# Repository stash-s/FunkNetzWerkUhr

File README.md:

# FunkNetzWerkUhr
ESP8266 IN-12 Nixie lamp netwok clock

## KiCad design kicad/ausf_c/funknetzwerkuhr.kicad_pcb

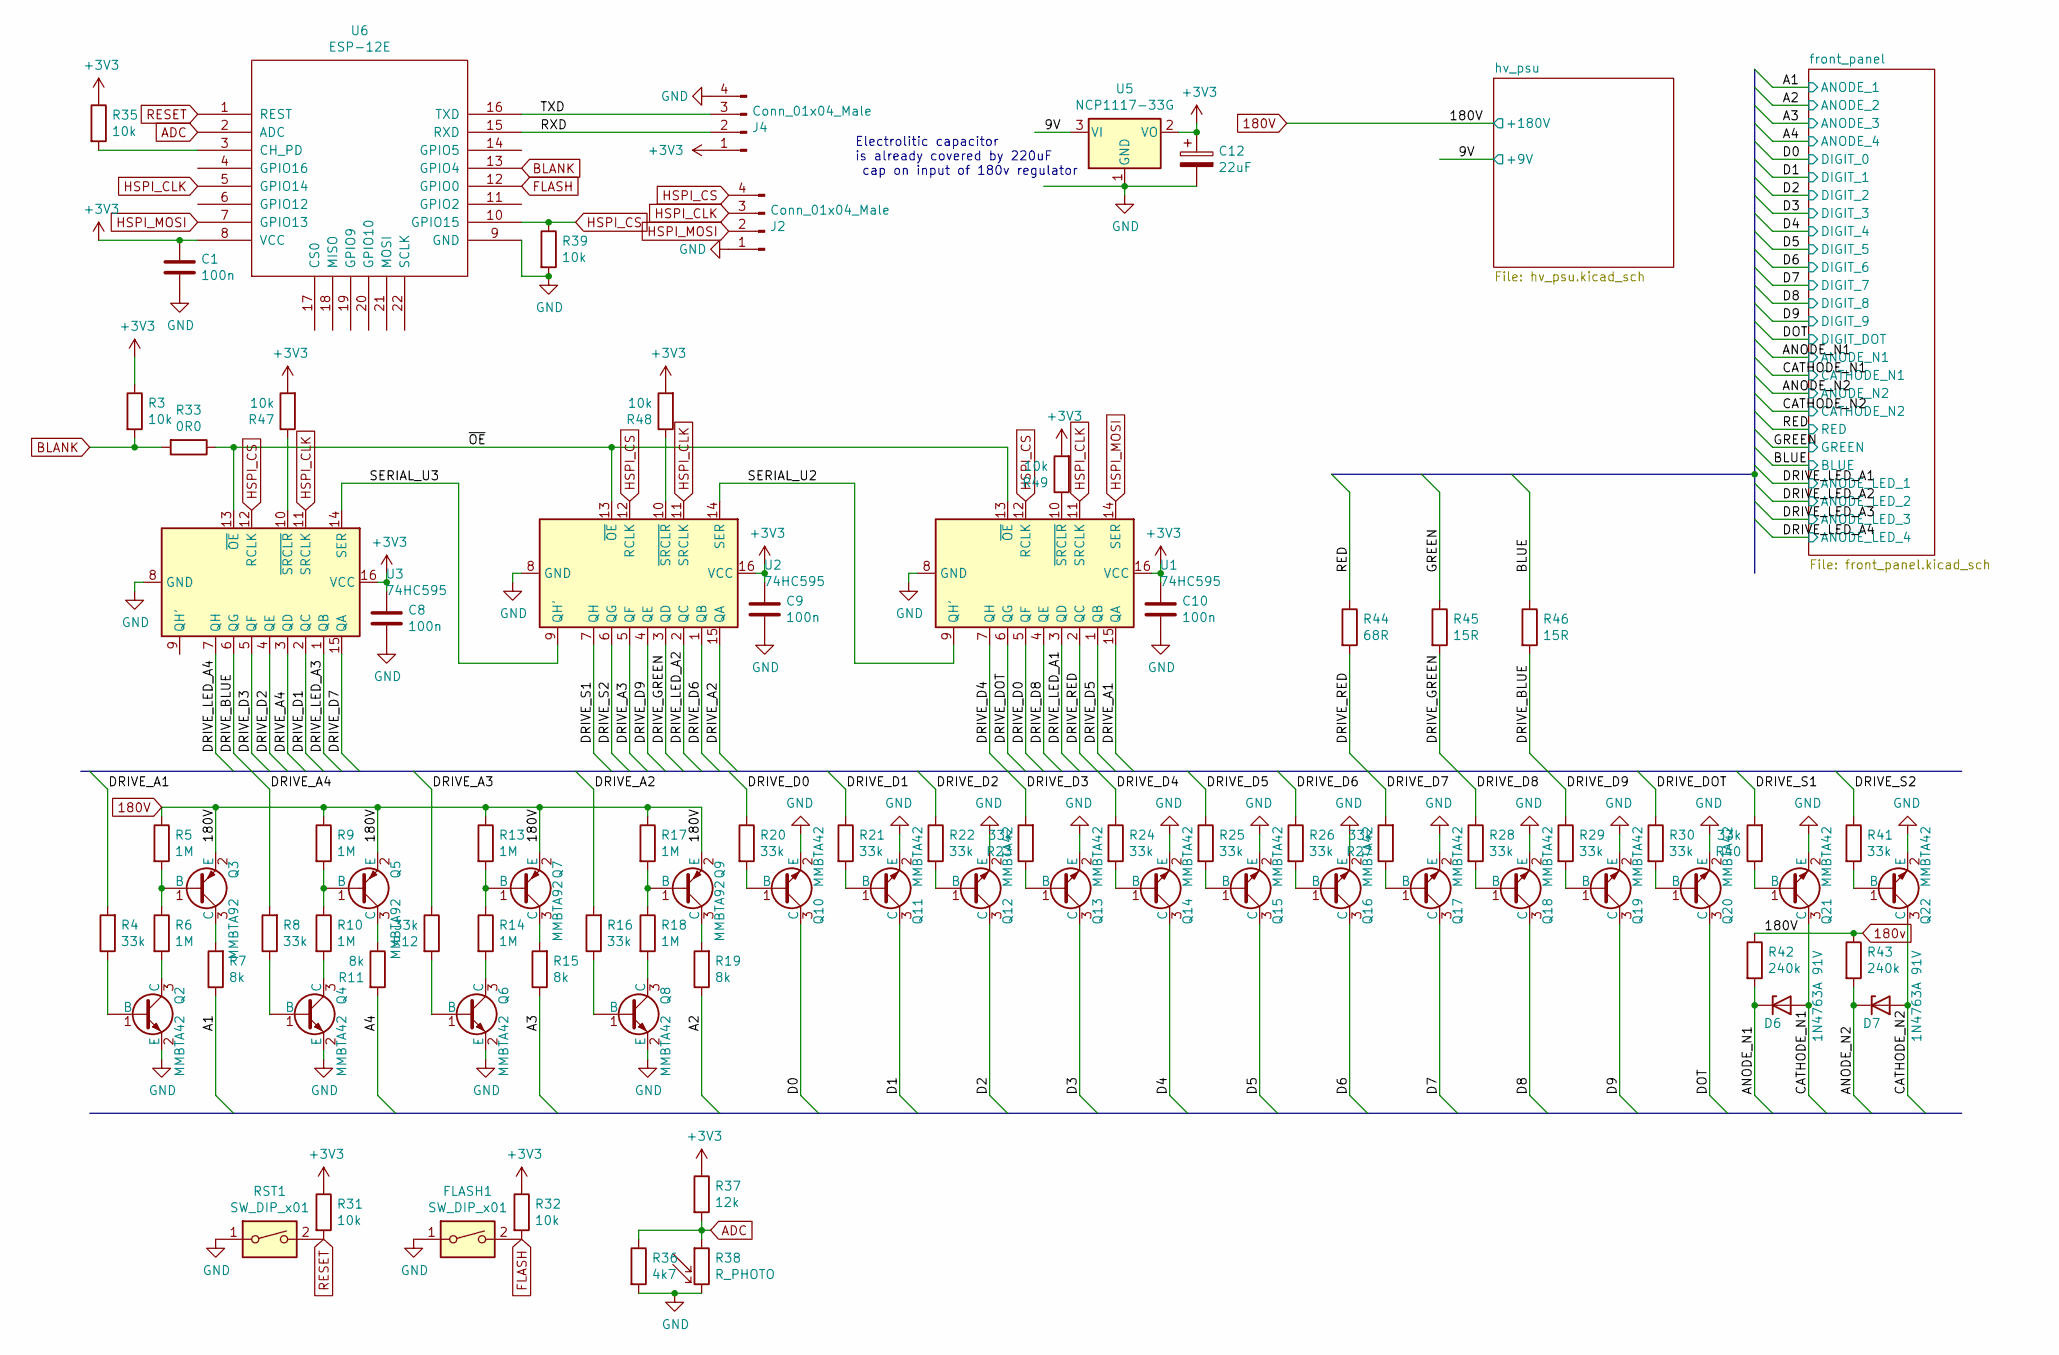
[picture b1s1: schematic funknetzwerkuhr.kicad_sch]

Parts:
C1, C8, C9, C10: 100n; C_1206_3216Metric_Pad1.42x1.75mm_HandSolder
C12: 22uF; CP_Radial_D6.3mm_P2.50mm
D6, D7: 1N4763A 91V; D_MiniMELF_Handsoldering
FLASH1: SW_DIP_x01; SW_PUSH-12mm
J2: Conn_01x04_Male; PinHeader_1x04_P2.54mm_Vertical
J4: Conn_01x04_Male; PinHeader_1x04_P2.54mm_Horizontal
Q2, Q4, Q6, Q8, Q10, Q11, Q12, Q13, Q14, Q15, Q16, Q17, Q18, Q19, Q20, Q21, Q22: MMBTA42; MPSA42-TSOT-23_HandSoldering
Q3, Q5, Q7, Q9: MMBTA92; MPSA92-TSOT-23_HandSoldering
R3, R31, R32, R35, R39, R47, R48, R49: 10k; R_0805_2012Metric_Pad1.15x1.40mm_HandSolder_Value
R4, R8, R12, R16, R20, R21, R22, R23, R24, R25, R26, R27, R28, R29, R30, R40, R41: 33k; R_0805_2012Metric_Pad1.15x1.40mm_HandSolder_Value
R5, R6, R9, R10, R13, R14, R17, R18: 1M; R_0805_2012Metric_Pad1.15x1.40mm_HandSolder_Value
R7, R11, R15, R19: 8k; R_0805_2012Metric_Pad1.15x1.40mm_HandSolder_Value
R33: 0R0; R_0805_2012Metric_Pad1.15x1.40mm_HandSolder_Value
R36: 4k7; R_0805_2012Metric_Pad1.15x1.40mm_HandSolder_Value
R37: 12k; R_0805_2012Metric_Pad1.15x1.40mm_HandSolder_Value
R38: R_PHOTO; R_LDR_4.9x4.2mm_P2.54mm_Vertical
R42, R43: 240k; R_0805_2012Metric_Pad1.15x1.40mm_HandSolder_Value
R44: 68R; R_0805_2012Metric_Pad1.15x1.40mm_HandSolder_Value
R45, R46: 15R; R_0805_2012Metric_Pad1.15x1.40mm_HandSolder_Value
RST1: SW_DIP_x01; SW_PUSH-12mm
U1, U2, U3: 74HC595; SOIC-16_3.9x9.9mm_P1.27mm
U5: NCP1117-33G; DPACK2
U6: ESP-12E; ESP-12E_SMD

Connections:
180V: Q3.2 (E), Q5.2 (E), Q7.2 (E), Q9.2 (E), R5.1, R9.1, R13.1, R17.1, R42.1, R43.1; also elsewhere on the board
+3V3: C1.1, C8.1, C9.1, C10.1, C12.1, J4.1, R3.1, R31.1, R32.1, R35.1, R37.1, R47.2, R48.2, R49.2, U1.16 (VCC), U2.16 (VCC), U3.16 (VCC), U5.2 (VO), U6.8 (VCC)
+9V: U5.3 (VI); also elsewhere on the board
/A1: R7.1; also elsewhere on the board
/A2: R19.1; also elsewhere on the board
/A3: R15.1; also elsewhere on the board
/A4: R11.2; also elsewhere on the board
/ANODE_N1: D6.1 (K), R42.2; also elsewhere on the board
/ANODE_N2: D7.1 (K), R43.2; also elsewhere on the board
/BLUE: R46.1; also elsewhere on the board
/CATHODE_N1: D6.2 (A), Q21.3 (C); also elsewhere on the board
/CATHODE_N2: D7.2 (A), Q22.3 (C); also elsewhere on the board
/D0: Q10.3 (C); also elsewhere on the board
/D1: Q11.3 (C); also elsewhere on the board
/D2: Q12.3 (C); also elsewhere on the board
/D3: Q13.3 (C); also elsewhere on the board
/D4: Q14.3 (C); also elsewhere on the board
/D5: Q15.3 (C); also elsewhere on the board
/D6: Q16.3 (C); also elsewhere on the board
/D7: Q17.3 (C); also elsewhere on the board
/D8: Q18.3 (C); also elsewhere on the board
/D9: Q19.3 (C); also elsewhere on the board
/DOT: Q20.3 (C); also elsewhere on the board
/DRIVE_A1: R4.2, U1.15 (QA)
/DRIVE_A2: R16.2, U2.15 (QA)
/DRIVE_A3: R12.1, U2.5 (QF)
/DRIVE_A4: R8.2, U3.3 (QD)
/DRIVE_BLUE: R46.2, U3.6 (QG)
/DRIVE_D0: R20.1, U1.5 (QF)
/DRIVE_D1: R21.1, U3.2 (QC)
/DRIVE_D2: R22.1, U3.4 (QE)
/DRIVE_D3: R23.2, U3.5 (QF)
/DRIVE_D4: R24.1, U1.7 (QH)
/DRIVE_D5: R25.1, U1.1 (QB)
/DRIVE_D6: R26.1, U2.1 (QB)
/DRIVE_D7: R27.2, U3.15 (QA)
/DRIVE_D8: R28.1, U1.4 (QE)
/DRIVE_D9: R29.1, U2.4 (QE)
/DRIVE_DOT: R30.1, U1.6 (QG)
/DRIVE_GREEN: R45.2, U2.3 (QD)
/DRIVE_LED_A1: U1.3 (QD); also elsewhere on the board
/DRIVE_LED_A2: U2.2 (QC); also elsewhere on the board
/DRIVE_LED_A3: U3.1 (QB); also elsewhere on the board
/DRIVE_LED_A4: U3.7 (QH); also elsewhere on the board
/DRIVE_RED: R44.2, U1.2 (QC)
/DRIVE_S1: R40.2, U2.7 (QH)
/DRIVE_S2: R41.1, U2.6 (QG)
/GREEN: R45.1; also elsewhere on the board
/RED: R44.1; also elsewhere on the board
/RXD: J4.2, U6.15 (RXD)
/SERIAL_U2: U1.9 (QH'), U2.14 (SER)
/SERIAL_U3: U2.9 (QH'), U3.14 (SER)
/TXD: J4.3, U6.16 (TXD)
/~OE: R33.1, U1.13 (~OE), U2.13 (~OE), U3.13 (~OE)
ADC: R36.1, R37.2, R38.1, U6.2 (ADC)
BLANK: R3.2, R33.2, U6.13 (GPIO4); also elsewhere on the board
FLASH: FLASH1.2, R32.2, U6.12 (GPIO0)
GND: C1.2, C8.2, C9.2, C10.2, C12.2, FLASH1.1, J2.1, J4.4, Q2.2 (E), Q4.2 (E), Q6.2 (E), Q8.2 (E), Q10.2 (E), Q11.2 (E), Q12.2 (E), Q13.2 (E), Q14.2 (E), Q15.2 (E), Q16.2 (E), Q17.2 (E), Q18.2 (E), Q19.2 (E), Q20.2 (E), Q21.2 (E), Q22.2 (E), R36.2, R38.2, R39.2, RST1.1, U1.8 (GND), U2.8 (GND), U3.8 (GND), U5.1 (GND), U6.9 (GND); also elsewhere on the board
HSPI_CLK: J2.3, U1.11 (SRCLK), U2.11 (SRCLK), U3.11 (SRCLK), U6.5 (GPIO14)
HSPI_CS: J2.4, R39.1, U1.12 (RCLK), U2.12 (RCLK), U3.12 (RCLK), U6.10 (GPIO15)
HSPI_MOSI: J2.2, U1.14 (SER), U6.7 (GPIO13)
unnamed: Q2.1 (B), R4.1
unnamed: Q2.3 (C), R6.2
unnamed: Q3.1 (B), R5.2, R6.1
unnamed: Q3.3 (C), R7.2
unnamed: Q4.1 (B), R8.1
unnamed: Q4.3 (C), R10.2
unnamed: Q5.1 (B), R9.2, R10.1
unnamed: Q5.3 (C), R11.1
unnamed: Q6.1 (B), R12.2
unnamed: Q6.3 (C), R14.2
unnamed: Q7.1 (B), R13.2, R14.1
unnamed: Q7.3 (C), R15.2
unnamed: Q8.1 (B), R16.1
unnamed: Q8.3 (C), R18.2
unnamed: Q9.1 (B), R17.2, R18.1
unnamed: Q9.3 (C), R19.2
unnamed: Q10.1 (B), R20.2
unnamed: Q11.1 (B), R21.2
unnamed: Q12.1 (B), R22.2
unnamed: Q13.1 (B), R23.1
unnamed: Q14.1 (B), R24.2
unnamed: Q15.1 (B), R25.2
unnamed: Q16.1 (B), R26.2
unnamed: Q17.1 (B), R27.1
unnamed: Q18.1 (B), R28.2
unnamed: Q19.1 (B), R29.2
unnamed: Q20.1 (B), R30.2
unnamed: Q21.1 (B), R40.1
unnamed: Q22.1 (B), R41.2
unnamed: R35.2, U6.3 (CH_PD)
unnamed: R47.1, U3.10 (~SRCLR)
unnamed: R48.1, U2.10 (~SRCLR)
unnamed: R49.1, U1.10 (~SRCLR)
RESET: R31.2, RST1.2, U6.1 (REST)

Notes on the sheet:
Electrolitic capacitor is already covered by 220uF cap on input of 180v regulator

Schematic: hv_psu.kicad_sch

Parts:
C2, C3: 100n; C_1206_3216Metric_Pad1.42x1.75mm_HandSolder
C4: 220uF,25V; CP_Radial_D10.0mm_P2.50mm_P5.00mm
C5: 4.7uF,250V; CP_Radial_D8.0mm_P3.50mm
C7: 100n,250V; C_Rect_L16.5mm_W4.7mm_P15.00mm_MKT
D1: ES2J; D_SMB_Handsoldering
J1: Jack-DC; AliExpress55mmBarelJack
J3: Conn_01x02_Male; PinHeader_1x02_P2.54mm_Vertical
L1: L; L_Toroid_Vertical_L14.0mm_W6.3mm_P4.57mm_Pulse_A
Q1: IRF640; TO-263-2
R1: 1.5M; R_1206_3216Metric_Pad1.42x1.75mm_HandSolder
R1a1: 2.7k; R_0805_2012Metric_Pad1.15x1.40mm_HandSolder_Value
R2: 10k; R_0805_2012Metric_Pad1.15x1.40mm_HandSolder_Value
R34: 0R0; R_0805_2012Metric_Pad1.15x1.40mm_HandSolder_Value
RSENSE1: 0R1; R_2512_6332Metric_Pad1.52x3.35mm_HandSolder
U4: max1771; PowerIntegrations_SO-8

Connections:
180V: C5.1, C7.1, D1.1 (K), J3.2, R1.1; also elsewhere on the board
+9V: C2.1, C4.1, J1.1, L1.1, U4.2 (VCC); also elsewhere on the board
/hv_psu/SENSE: Q1.3 (S), RSENSE1.1, U4.8 (CS)
BLANK: R34.2; also elsewhere on the board
GND: C2.2, C3.2, C4.2, C5.2, C7.2, J1.2, J1.3, J3.1, R2.2, RSENSE1.2, U4.6 (AGND), U4.7 (GND); also elsewhere on the board
unnamed: C3.1, U4.5 (REF)
unnamed: D1.2 (A), L1.2, Q1.2 (D)
unnamed: Q1.1 (G), U4.1 (EXT)
unnamed: R1.2, R1a1.1, U4.3 (FB)
unnamed: R1a1.2, R2.1
unnamed: R34.1, U4.4 (SHDN)

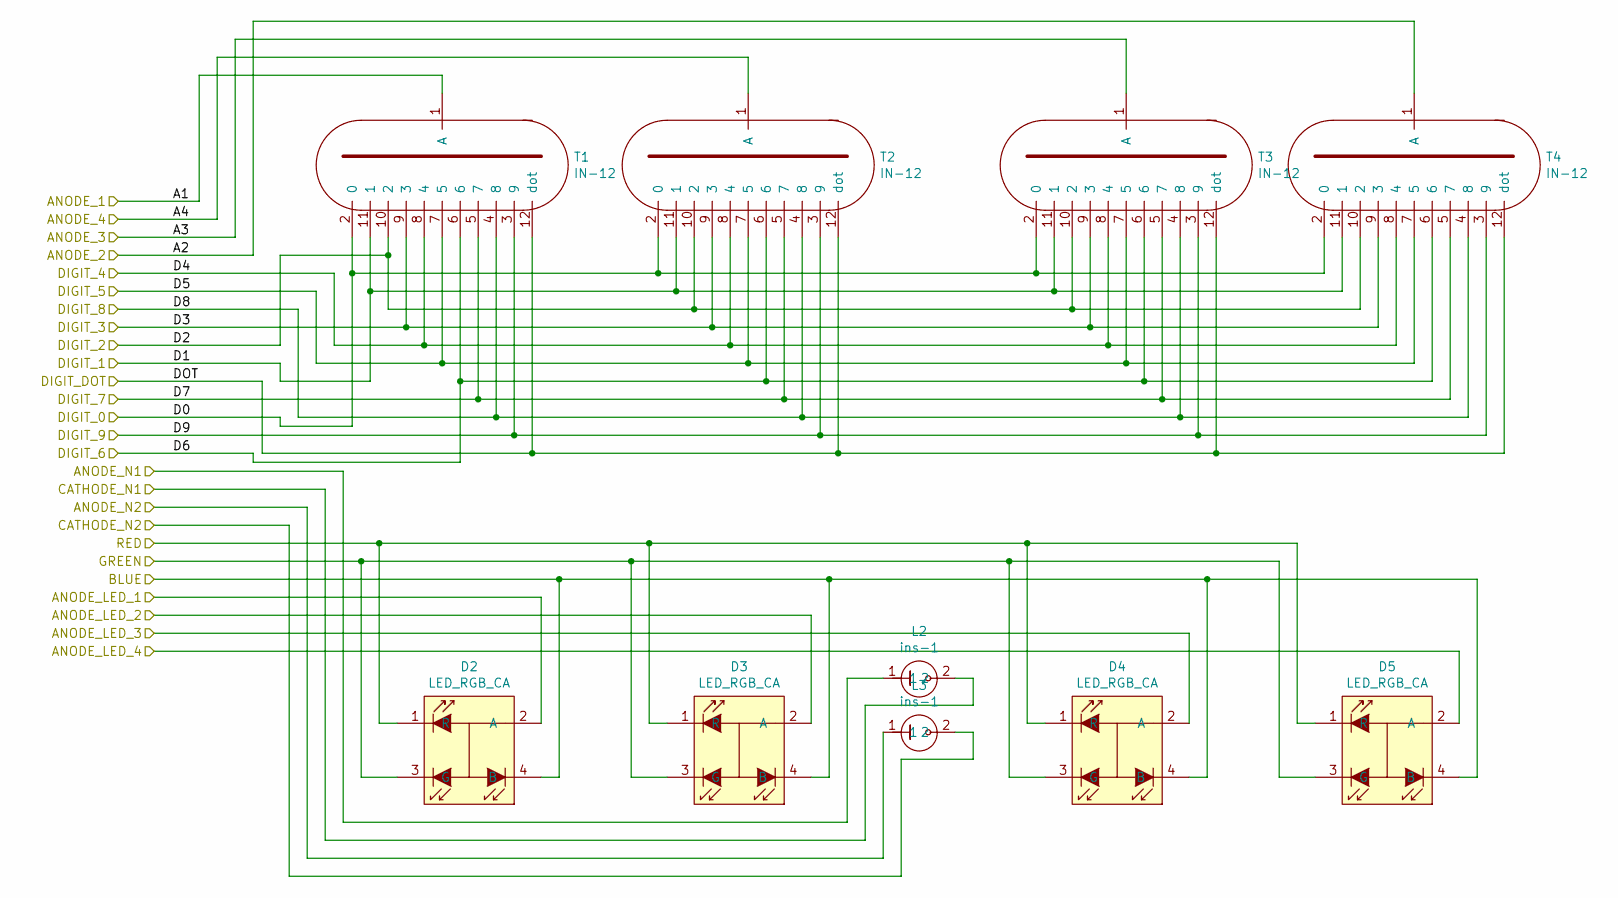
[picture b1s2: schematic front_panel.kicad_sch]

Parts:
D2, D3, D4, D5: LED_RGB_CA; LED_3528_3.5x2.8mm
L2, L3: ins-1
T1, T2, T3, T4: IN-12; IN-12_0.8mm_simple

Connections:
/A1: T1.1 (A); also elsewhere on the board
/A2: T4.1 (A); also elsewhere on the board
/A3: T3.1 (A); also elsewhere on the board
/A4: T2.1 (A); also elsewhere on the board
/ANODE_N1: L2.1; also elsewhere on the board
/ANODE_N2: L3.1; also elsewhere on the board
/BLUE: D2.4 (B), D3.4 (B), D4.4 (B), D5.4 (B); also elsewhere on the board
/CATHODE_N1: L2.2; also elsewhere on the board
/CATHODE_N2: L3.2; also elsewhere on the board
/D0: T1.2 (0), T2.2 (0), T3.2 (0), T4.2 (0); also elsewhere on the board
/D1: T1.11 (1), T2.11 (1), T3.11 (1), T4.11 (1); also elsewhere on the board
/D2: T1.10 (2), T2.10 (2), T3.10 (2), T4.10 (2); also elsewhere on the board
/D3: T1.9 (3), T2.9 (3), T3.9 (3), T4.9 (3); also elsewhere on the board
/D4: T1.8 (4), T2.8 (4), T3.8 (4), T4.8 (4); also elsewhere on the board
/D5: T1.7 (5), T2.7 (5), T3.7 (5), T4.7 (5); also elsewhere on the board
/D6: T1.6, T2.6, T3.6, T4.6; also elsewhere on the board
/D7: T1.5 (7), T2.5 (7), T3.5 (7), T4.5 (7); also elsewhere on the board
/D8: T1.4 (8), T2.4 (8), T3.4 (8), T4.4 (8); also elsewhere on the board
/D9: T1.3 (9), T2.3 (9), T3.3 (9), T4.3 (9); also elsewhere on the board
/DOT: T1.12 (dot), T2.12 (dot), T3.12 (dot), T4.12 (dot); also elsewhere on the board
/DRIVE_LED_A1: D2.2 (A); also elsewhere on the board
/DRIVE_LED_A2: D3.2 (A); also elsewhere on the board
/DRIVE_LED_A3: D4.2 (A); also elsewhere on the board
/DRIVE_LED_A4: D5.2 (A); also elsewhere on the board
/GREEN: D2.3 (G), D3.3 (G), D4.3 (G), D5.3 (G); also elsewhere on the board
/RED: D2.1 (R), D3.1 (R), D4.1 (R), D5.1 (R); also elsewhere on the board

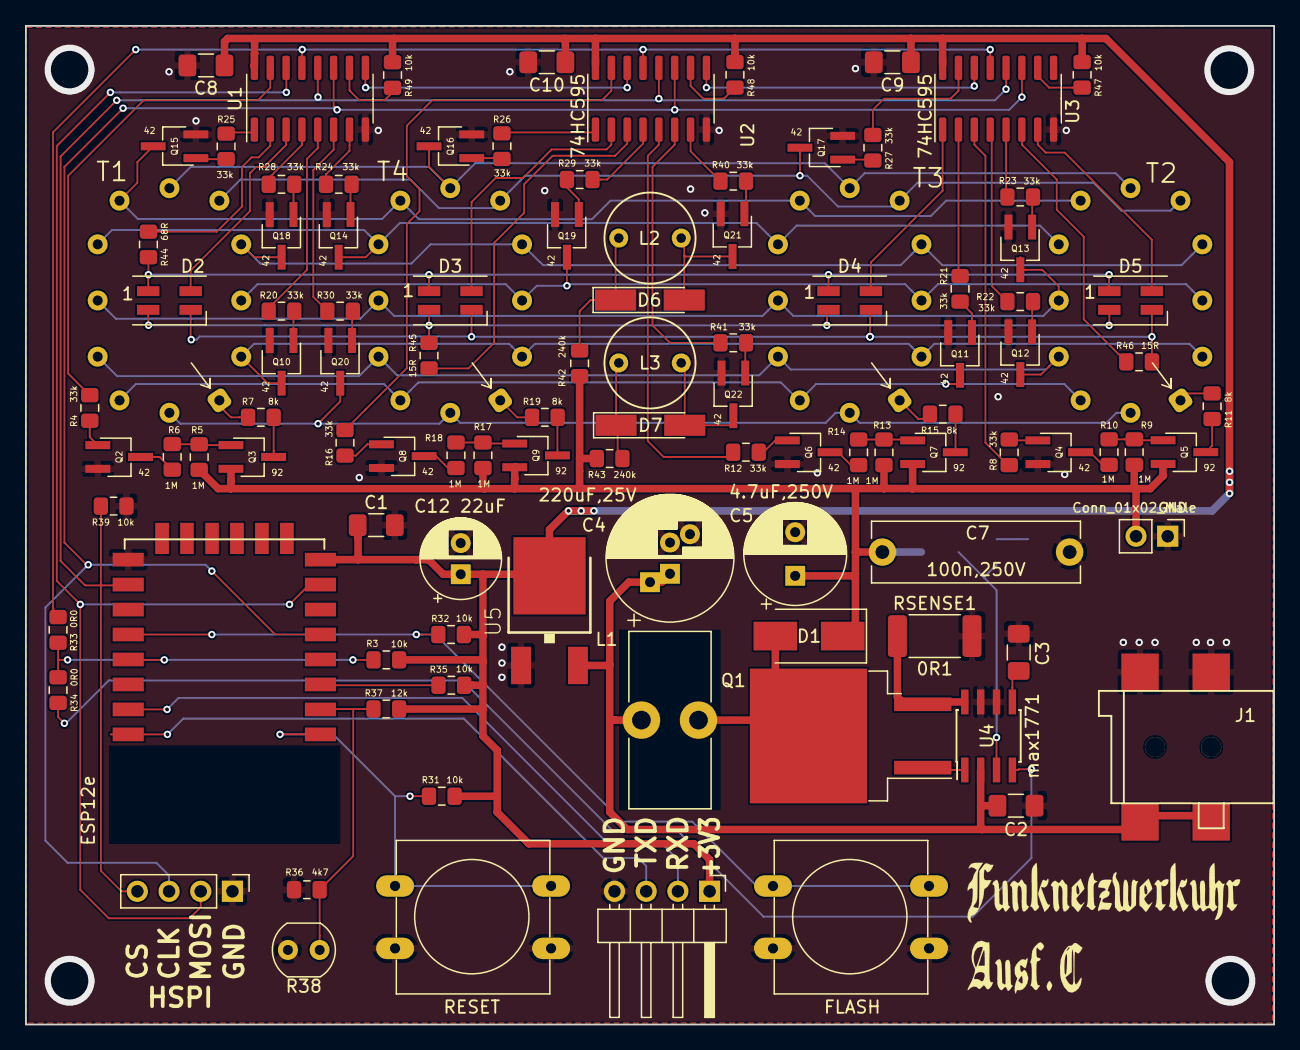
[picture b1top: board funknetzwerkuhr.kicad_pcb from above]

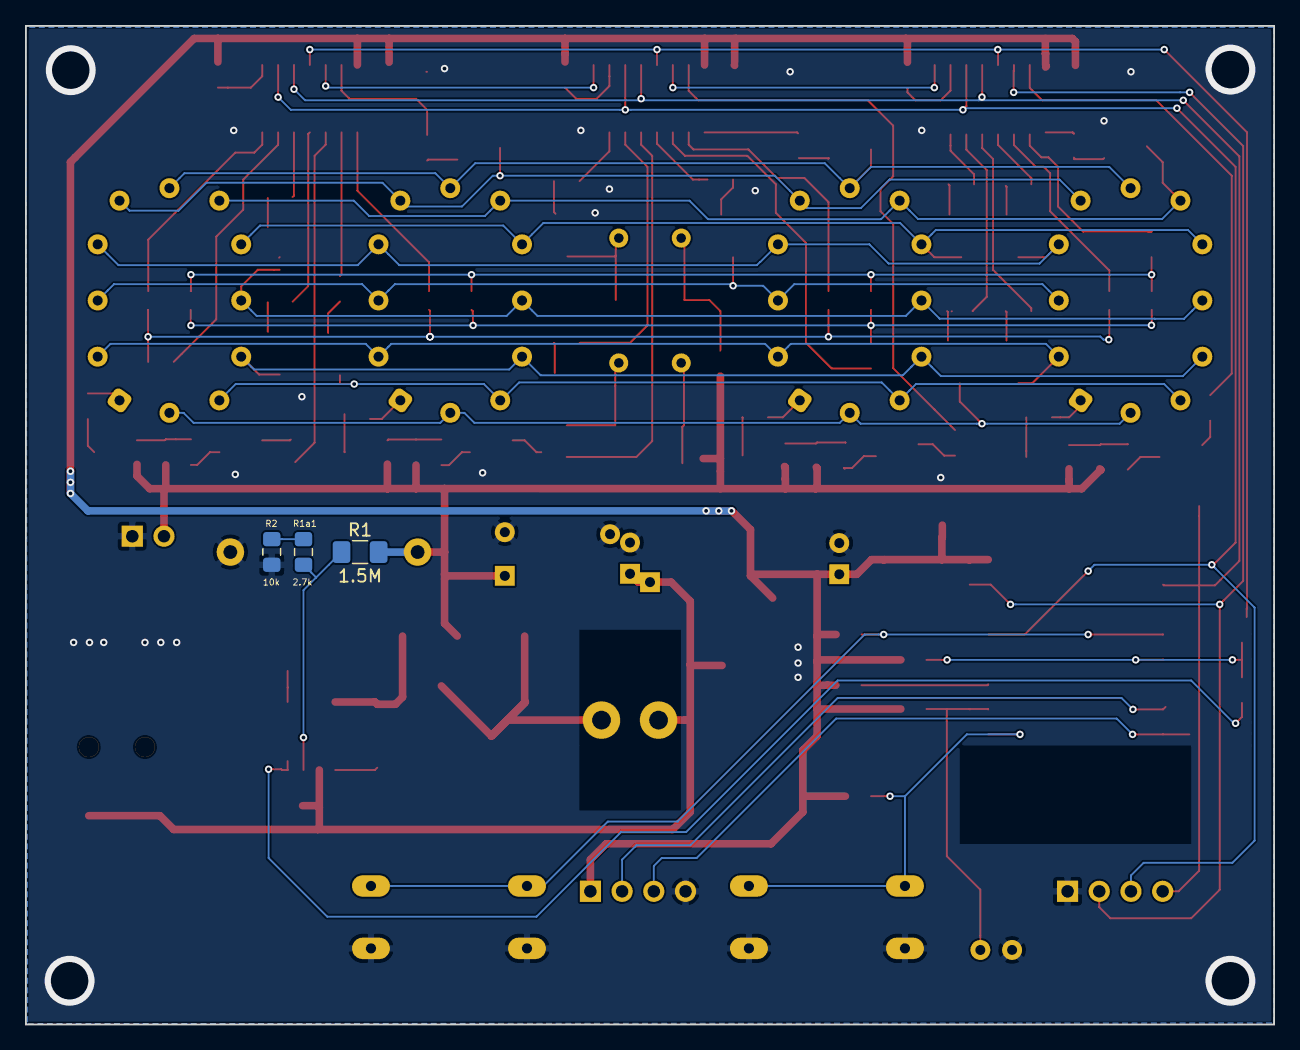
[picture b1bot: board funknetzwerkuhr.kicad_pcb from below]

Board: 2 copper layers, 100.0 x 80.0 mm, 109 parts (3 on the bottom side), 102 nets.

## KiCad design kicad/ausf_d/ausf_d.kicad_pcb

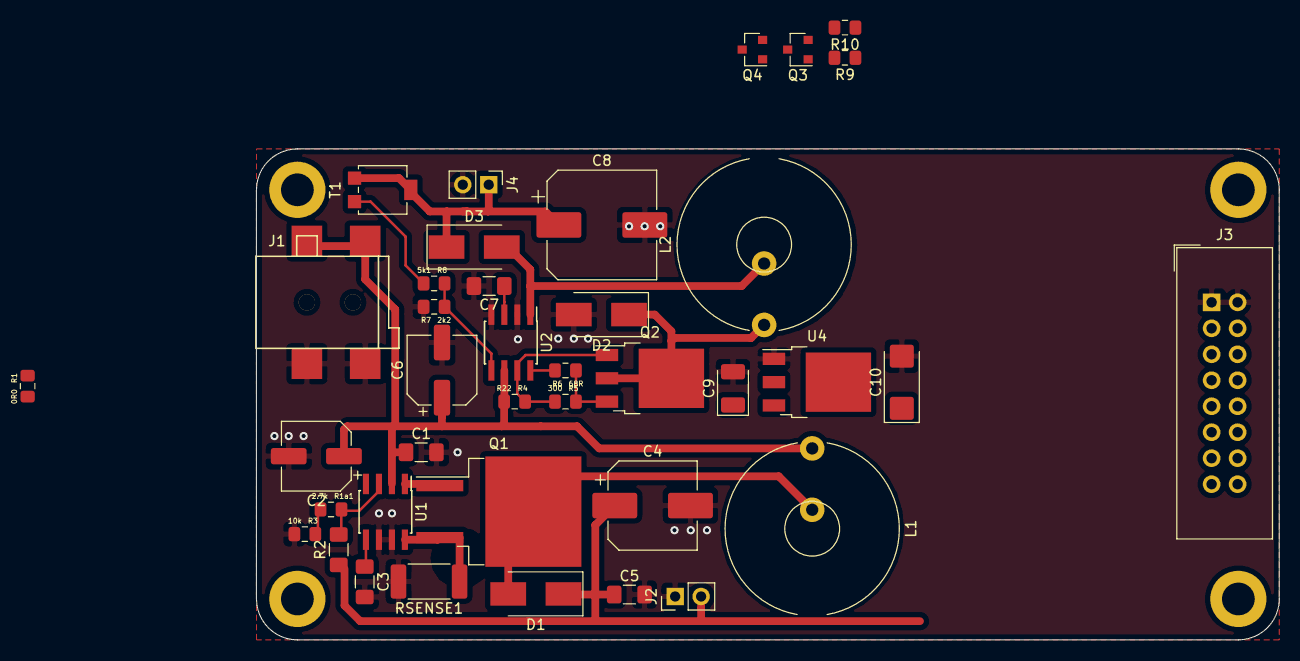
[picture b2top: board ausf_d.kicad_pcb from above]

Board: 2 copper layers, 100.0 x 48.0 mm, 40 parts (1 on the bottom side), 26 nets.

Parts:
C1, C3: 100n; C_1206_3216Metric_Pad1.42x1.75mm_HandSolder
C2: 220uF,25V; CP_Elec_6.3x7.7
C4: 4.7uF,250V; CP_Elec_8x10.5
C5: 100n,250V; C_1206_3216Metric_Pad1.42x1.75mm_HandSolder
C6: 100; CP_Elec_6.3x7.7
C7: 470pF; C_1206_3216Metric_Pad1.42x1.75mm_HandSolder
C8: 330; CP_Elec_10x14.3
C9: 10u; CP_EIA-3528-12_Kemet-T_Pad1.50x2.35mm_HandSolder
C10: 22u; CP_EIA-6032-28_Kemet-C_Pad2.25x2.35mm_HandSolder
D1: ES2J; D_SMB_Handsoldering
D2, D3: SS16T3G; D_SMB_Handsoldering
J1: Jack-DC; AliExpress55mmBarrelJack
J2: Conn_01x02_Male; PinHeader_1x02_P2.54mm_Vertical
J3: Conn_02x10_Odd_Even; IDC-Header_2x08_P2.54mm_Vertical
J4: Conn_01x02; PinHeader_1x02_P2.54mm_Vertical
L1: L; L_Toroid_Horizontal_D16.8mm_P6mm_AliExpress
L2: 300uH; L_Toroid_Horizontal_D16.8mm_P6mm_AliExpress
Q1: IRF640; TO-263-2
Q2: 2SD669AD-C; TO-252-3_TabPin2
Q3, Q4: BC847; SOT-23
R1: 0R0; R_0805_2012Metric_Pad1.15x1.40mm_HandSolder_Value
R1a1: 2.7k; R_0805_2012Metric_Pad1.15x1.40mm_HandSolder_Value
R2: 1.5M; R_1206_3216Metric_Pad1.42x1.75mm_HandSolder
R3: 10k; R_0805_2012Metric_Pad1.15x1.40mm_HandSolder_Value
R4: R22; R_0805_2012Metric_Pad1.15x1.40mm_HandSolder_Value
R5: 300; R_0805_2012Metric_Pad1.15x1.40mm_HandSolder_Value
R6: 68R; R_0805_2012Metric_Pad1.15x1.40mm_HandSolder_Value
R7: 2k2; R_0805_2012Metric_Pad1.15x1.40mm_HandSolder_Value
R8: 5k1; R_0805_2012Metric_Pad1.15x1.40mm_HandSolder_Value
R9, R10: 12k; R_0805_2012Metric_Pad1.15x1.40mm_HandSolder
RSENSE1: 0R1; R_2512_6332Metric_Pad1.52x3.35mm_HandSolder
T1: TRIM_EU-S64W; Potentiometer_Bourns_3314G_Vertical
U1: max1771; PowerIntegrations_SO-8
U2: MC34063AP; PowerIntegrations_SO-8
U3: ESP-12F; ESP-12E
U4: AMS1117CD-3.3; TO-252-3_TabPin2

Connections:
+9V: C1.1, C2.1, C6.1, C9.1, J1.1, J3.7, J3.8, L1.1, R4.2, U1.2, U2.6, U4.3
/+3V3: C10.1, J3.5, J3.6, U3.8, U4.2
/+FILAMENT_DC: C8.1, D3.1, J3.3, J3.4, J4.1, T1.1, T1.2
/+HVDC: C4.1, C5.1, D1.1, J2.2, J3.9, J3.10, R2.1
/DTR: Q4.2, R9.1
/GPIO0: Q4.3, U3.18
/RST: Q3.3, U3.1
/RTS: Q3.2, R10.1
/hv_psu/SENSE: Q1.3, RSENSE1.1, U1.8
GND: C1.2, C2.2, C3.2, C4.2, C5.2, C6.2, C7.2, C8.2, C9.2, C10.2, D2.2, J1.2, J1.3, J2.1, J3.1, J3.2, J4.2, R3.2, R7.1, RSENSE1.2, U1.6, U1.7, U2.2, U2.4, U3.15, U4.1
unnamed: C3.1, U1.5
unnamed: C7.1, U2.3
unnamed: D1.2, L1.2, Q1.2
unnamed: D2.1, L2.1, Q2.2
unnamed: D3.2, L2.2, U2.1
unnamed: Q1.1, U1.1
unnamed: Q2.1, R4.1, R5.2, U2.7
unnamed: Q2.3, R5.1, R6.2
unnamed: Q3.1, R9.2
unnamed: Q4.1, R10.2
unnamed: R1.1, U1.4
unnamed: R1a1.1, R2.2, U1.3
unnamed: R1a1.2, R3.1
unnamed: R6.1, U2.8
unnamed: R7.2, R8.1, U2.5
unnamed: R8.2, T1.3

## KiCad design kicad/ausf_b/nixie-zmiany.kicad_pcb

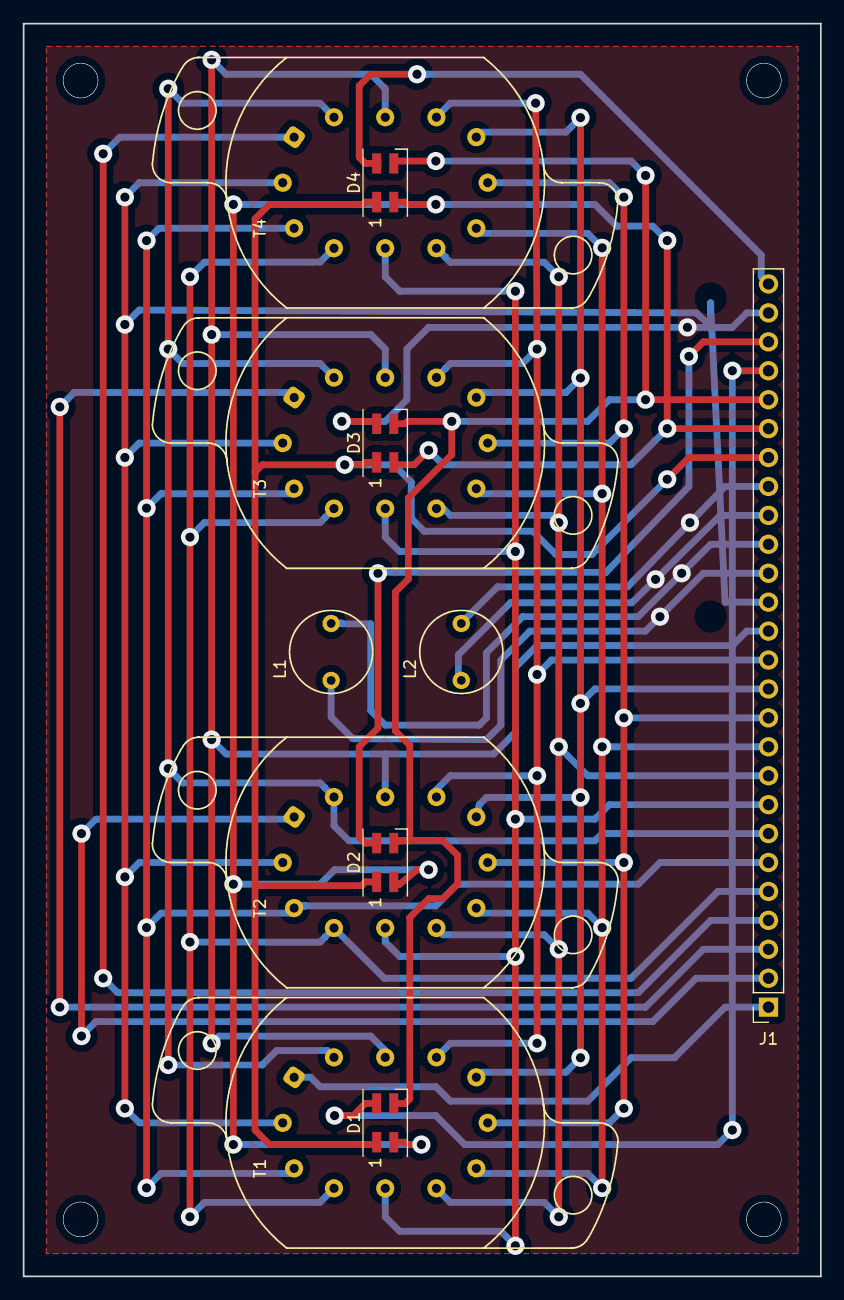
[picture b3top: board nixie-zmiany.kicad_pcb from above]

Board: 2 copper layers, 70.0 x 110.0 mm, 11 parts (0 on the bottom side), 26 nets.

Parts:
D1, D2, D3, D4: LED_RGB_CA; LED_3528_3.5x2.8mm
J1: Conn_01x26_Male; PinSocket_1x26_P2.54mm_Vertical
L1, L2: ins-1
T1, T2, T3, T4: IN-12; IN-12_0.8mm

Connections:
unnamed: D1.1, D2.1, D3.1, D4.1, J1.20
unnamed: D1.2, J1.23
unnamed: D1.3, D2.3, D3.3, D4.3, J1.21
unnamed: D1.4, D2.4, D3.4, D4.4, J1.22
unnamed: D2.2, J1.24
unnamed: D3.2, J1.25
unnamed: D4.2, J1.26
unnamed: J1.1, T1.1
unnamed: J1.2, T2.1
unnamed: J1.3, T3.1
unnamed: J1.4, T4.1
unnamed: J1.5, T1.10, T2.10, T3.10, T4.10
unnamed: J1.6, T1.11, T2.11, T3.11, T4.11
unnamed: J1.7, T1.2, T2.2, T3.2, T4.2
unnamed: J1.8, T1.9, T2.9, T3.9, T4.9
unnamed: J1.9, T1.8, T2.8, T3.8, T4.8
unnamed: J1.10, T1.7, T2.7, T3.7, T4.7
unnamed: J1.11, T1.6, T2.6, T3.6, T4.6
unnamed: J1.12, T1.5, T2.5, T3.5, T4.5
unnamed: J1.13, T1.4, T2.4, T3.4, T4.4
unnamed: J1.14, T1.3, T2.3, T3.3, T4.3
unnamed: J1.15, T1.12, T2.12, T3.12, T4.12
unnamed: J1.16, L1.1
unnamed: J1.17, L1.2
unnamed: J1.18, L2.1
unnamed: J1.19, L2.2

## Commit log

2018-07-26 Initial commit.
2018-07-28 Pulled all into one schematic - don't know yet if this is a good idea.
2018-08-02 Schematic nearly done, need to add programming header.
2018-08-02 Added 1st prototype of clock's brains.
2018-08-05 Schematic complete. PCB nearly done.
2018-08-06 First final draft ready (Ausf B)
2018-08-08 Nearly done.
2018-08-31 Completely broken now
2018-08-31 Nothing works now.
2018-09-01 Works again.
2018-09-01 Working with colors
2018-09-01 Cycle colors.
2018-09-02 Light sensor adjusts brightness to ambient light.
2018-09-03 Making place for new pcb (ausf c)
2018-09-03 Removed redundant .gitignore
2018-09-09 PSU does not fit into the outline.
2018-09-11 Minor automated update.
2018-10-07 Added vscode project file.
2018-10-07 Refactored - create an abstract superclass
2018-10-20 Added nice typedef for LightSensor
2018-10-20 Added NTP Client submodule
2018-10-20 Added NTP Client module to work on modified (events added) 3rd party module.
2018-10-20 Pointed module NTPClient to proper (forked) repository.
2018-10-20 Use NTP events to flag that update was performed.
2018-10-21 Added slot machine effect.
2018-10-21 Restart after failed NTP connection attempts.
2018-10-21 Added timeout waiting for AP autoconnect.
2018-11-02 Changed to winter time zone.
2018-11-02 Added new hw revision.
2018-11-08 Separated backlight color setting and animation start/stop.
2019-05-02 Nearly done Ausf C PCB layout.
2019-05-03 Ausf C PCB version ordered.
2019-05-03 Additional save.
2019-05-12 First attempt at universal clock mainboard.
2019-05-12 Fixed WIP after cleanup.
2019-05-12 Working version of ausf D is on the branch.
2019-05-12 Changed linear stabilizer caps to tantallum type.
2019-05-14 Made version work with Ausf. A and Ausf. C
2019-08-12 Uodated chassis drawing
2020-11-01 Cleanup and use custom NTP Client
2020-11-01 Works for Ausf B and C hardware.
2020-11-01 Reference global Github version of NTPClient
2020-11-01 Light Sensor fixed for Ausf B and C
2020-11-01 Whitespace
2020-11-04 Three versions of harware are supported.
2020-11-04 Cosmetic changes
2020-11-04 Fixed incomplete merge.
2020-11-04 Removed link to custom library. Use git dependency instead.
2020-11-04 Removed temporary Kicad files.
2020-11-04 Minor edits
2020-11-05 Corrected 4 digit in ausf C version.
2020-11-05 Opened ausf_c with newer Kicad version.
2021-06-09 Switched from NTPClient to ezTime library
2021-06-09 Switch from NTPTime to ezTime library.
2021-06-09 Switched from NTPTime to ezTime
2021-06-09 Changed NTPClient to ezTime
2021-06-12 Switched to asynchronous web server and added endpoints to reset configuration.
2021-11-27 Ausf C chassis ready
2021-11-27 Tweak lamp hole size
2021-11-27 cache updated
2021-12-01 Red pulse changed
2021-12-01 Red highlight cycling tweak.
2022-11-16 Added Ausf C layout
